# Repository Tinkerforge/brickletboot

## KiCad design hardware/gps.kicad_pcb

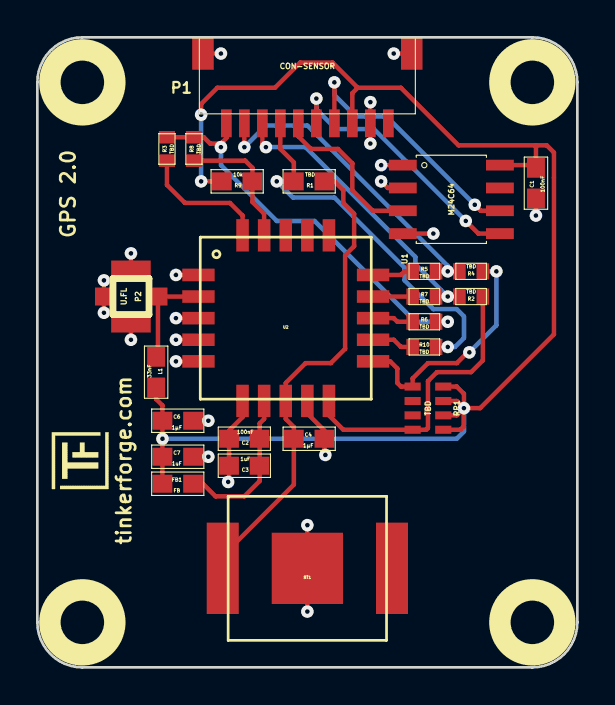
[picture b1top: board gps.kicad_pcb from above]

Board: 2 copper layers, 30.0 x 35.0 mm, 29 parts (1 on the bottom side), 20 nets.

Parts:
BT1: Battery; BATTERY_HOLDER_2998
C1, C2: 100nF; 0603E
C3, C7: 1uF; 0603E
C4, C6: 1µF; 0603E
FB1: FB; 0603E
L1: 33nF; 0603E
P1: CON-SENSOR
P2: U.FL; U.FL-CON
R1: TBD; 0603E
R2, R3, R4, R5, R6, R7, R8, R10: TBD; 0402E
R9: 10k; 0603E
RP1: TBD; 4X0603
U1: M24C64; SOIC8
U2: FireFlyX1
U3, U4, U5, U6: DRILL; DRILL_NP
VAL: CE_5mm

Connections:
+BATT: BT1.1, C4.2, R1.2, U2.8
GND: BT1.2, C1.2, C2.1, C3.1, C4.1, C6.1, C7.1, P1.2, P1.EP, P2.2, U1.1, U1.2, U1.4, U2.1, U2.3, U2.4, U2.5, U2.6, U2.9
unnamed: C2.2, C3.2, FB1.1, U2.7
unnamed: L1.2, P2.1, U2.2
unnamed: P1.6, U1.3
unnamed: P1.7, R1.1, R10.1
unnamed: P1.8, R2.1, R7.1
unnamed: P1.9, R4.1, R5.1
unnamed: P1.10, R3.1, R6.1, R8.1
unnamed: R2.2, RP1.5, U2.10
unnamed: R3.2, U2.20
unnamed: R4.2, RP1.8, U2.11
unnamed: R5.2, U2.15
unnamed: R6.2, U2.13
unnamed: R7.2, U2.14
unnamed: R8.2, R9.2, U2.19
unnamed: R10.2, U2.12
SCL: P1.4, U1.6
SDA: P1.5, U1.5
VCC: C1.1, C6.2, C7.2, FB1.2, L1.1, P1.3, R9.1, RP1.1, RP1.2, RP1.3, RP1.4, U1.8

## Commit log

2016-02-17 prototype of gps v2 bricklet
2016-02-17 Fix readme
2016-04-29 Add minimum viable firmware based on new bricklib2
    This is currently just a blinking LED and debug output.
2016-04-29 Change bricklib to bricklib2
2016-08-31 Add initial implementation of SPITFP protocol
    This is not yet optimized for small flash memory footprint.
    The next step is to heavily optimize this so it fits in 4 or
    8kb of flash.
2016-09-02 Lots of memory optimizations (fits in 8kb now)
2016-09-02 Remove brickletboot (is now in bricklib2)
2016-09-02 Make configs changable by firmware
2016-09-02 Use correct firmware size (without crc)
2016-09-02 Add spitfp_init to firmware_entry function
2016-09-02 Add sane defaults
2016-09-02 Add bootloader version
2016-09-02 Use config.h (configured through custom config)
2016-09-02 Remove accidentially commited files
2016-09-02 Append checksum to firmware
2016-09-02 Remove GPS hardware
2016-09-06 Handle resets correctly to allow for message answsers
2016-09-06 Use tinywdt and tinynvm instead of wdt and nvm
2016-09-08 Add comment for wait states
2016-09-08 Add fake SysTick for bootloader mode
2016-09-08 Use proper return values
2016-09-08 If we come from firmware mode and want to erase a row to go to bootloader mode, we have to first call tinynvm_init
2016-09-09 Add c files that are to be commented in for testing
2016-09-09 Add protocol documentation
2016-09-09 Add TODO
2016-09-09 Erase row only if necessary (directly before flash)
2016-09-09 Add optional check for UID
2016-09-15 Call handle message function with correct return_message
2016-09-22 Add configs
2016-09-22 Add overwrites
2016-09-22 Add NOSTARTFILES flag for bootloader compilation
2016-09-22 Use descriptor array instead of additional pointer
2016-09-22 Update configs
2016-09-22 Remove temperature API for now (will likely not fit)
2016-09-22 Add support for bootloader functions
2016-11-15 Fix toolchain path
